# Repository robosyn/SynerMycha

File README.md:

# SynerMycha

Projekt micromouse'a

## BOM

|Qty|Value|Device|Package|Parts|Description|
|---|-----|------|-------|-----|-----------|
|3|Blue|LEDCHIP-LED0603|CHIP-LED0603|LED1,LED2,LED3||
|1|Red|LEDCHIPLED_0603|CHIPLED_0603|LED5||
|1||PINHD-1X2|1X02|POWER||
|1||PINHD-1X5|1X05|JP3||
|1||PINHD-2X3|2X03|JP1||
|1||SPDT-PTH-11.6X4.0MM|SPDT_PTH_11.6X4.0MM|S1||
|12|100nF|CAPACITOR_SMD_0603|C0603K|C5,C6,C16,C18,C19,C21,C23,C24,C27,C29,C31,C36||
|1|100nF|CPOL-EUSMCA|SMC_A|C1||
|7|10k|RESISTOR_SMD_0603|R0603|R8,R15,R16,R25,R26,R27,R28||
|1|16Mhz|CRYSTAL_SMALL";|Y1|12.0MHzCrystal||
|2|18pF|CAPACITOR_SMD_0603|C0603K|C8,C9||
|2|1k|R-EU_R0603|R0603|R13,R14||
|5|1k|RESISTOR_SMD_0603|R0603|R2,R3,R4,R5,R7||
|1|270|RESISTOR_SMD_0603|R0603|R6||
|7|2k2|RESISTOR_SMD_0603|R0603|R1,R9,R10,R11,R12,R23,R24||
|3|330|R-EU_R0402|R0402|R17,R18,R19||
|5|33uF|CPOL-EUC|PANASONIC_C|C3,C4,C7,C32,C34||
|2|ACS711|ACS712|SOIC127P600X175-8N|IC3,IC4||
|5|ADAFRUIT-VCNL4010|ADAFRUIT-VCNL4010|ADAFRUIT-VCNL4010|U$7,U$8,U$9,U$10,U$11||
|5|BC847|BC847|SOT23|T1,T2,T3,T4,T5||
|1|MICROMATCH-6|MICROMATCH-6|MICROMATCH-6|PROG-SWDIO||
|1|SPST-SMD-6.2MM|SPST-SMD-6.2MM|SPST_SMD_6.2MM|S2||
|2|AS5040|AS5040|AS5040|U$13,U$14||
|1|STM32F411RCT6|STM32F411RCT6|LQFP64|IC7||
|1|SWS004|SWS004|SMS-004|S3||
|2|TLE9201SG|TLE9201SG|PG-DSO-12-9|IC5,IC6||
|1|3V3|V_REG_317-DPACK|V-REG_DPACK|U2||
|2|N20BT06100:1|N20BT06100:1||||
|2|RW2isolarbotics|RW2isolarbotics||||
|2|300mAh|LiPol,Dualsky||||

## Linki do niektórych części

| Nazwa |kamami ID |cena (botland) |botland |electropark |tme |
| ------|:-----:|:-------------:|:------:|:----------:|:--:|
| N20 BT06              | 562730 | 19.9zł| https://botland.com.pl/pl/silniki-micro-n20-seria-mp-medium-power/12545-silnik-n20-bt05-micro-501-625rpm-12v.html | tylko oryginalne |  tylko oryginalne pololu|
| RW2i solarbotics      | 195993 | 24.9zł| https://botland.com.pl/pl/kola-z-oponami/24-kolo-solarbotics-rw2i-mocowane-wewnetrznie.html      | chwilowo niedostpne | brak|
| lipol 300mah dualsky  | brak   | 22.5zł| https://botland.com.pl/pl/akumulatory-li-pol/7876-pakiet-li-pol-dualsky-300mah-30c-2s-74v-6941047107403.html?search_query=300mAh&results=3    | wycofany | brak |
| stm32f411             | 233365 | brak  | chwilowo niedostępnu| 27.65 zł|https://www.tme.eu/pl/details/stm32f411rct6/mikrokontrolery-st/stmicroelectronics/|
| TLE9201               | brak   | brak  | brak |13.93zł| https://www.tme.eu/pl/details/tle9201sgauma1/drivery-silnikowe-i-pwm/infineon-technologies/ |
| VCNL4010              | brak   | 44zł  |   https://botland.com.pl/pl/cyfrowe-czujniki-odleglosci/4969-adafruit-vcnl4010-czujnik-odleglosci-i-swiatla-20cm-i2c.html?search_query=vcnl4010&results=1| |tylko chip bez płytki na specjalne zamówienie |

~ oferta: 
~ 35zł https://www.elfadistrelec.pl/pl/czujnik-zblizeniowy-swiatla-vcnl4010-adafruit-466/p/30139237
plus ~50 za przesyłke
TLE9210 dostępne w labie

### CADLAB 

View this project on [CADLAB.io](https://cadlab.io/project/1503).

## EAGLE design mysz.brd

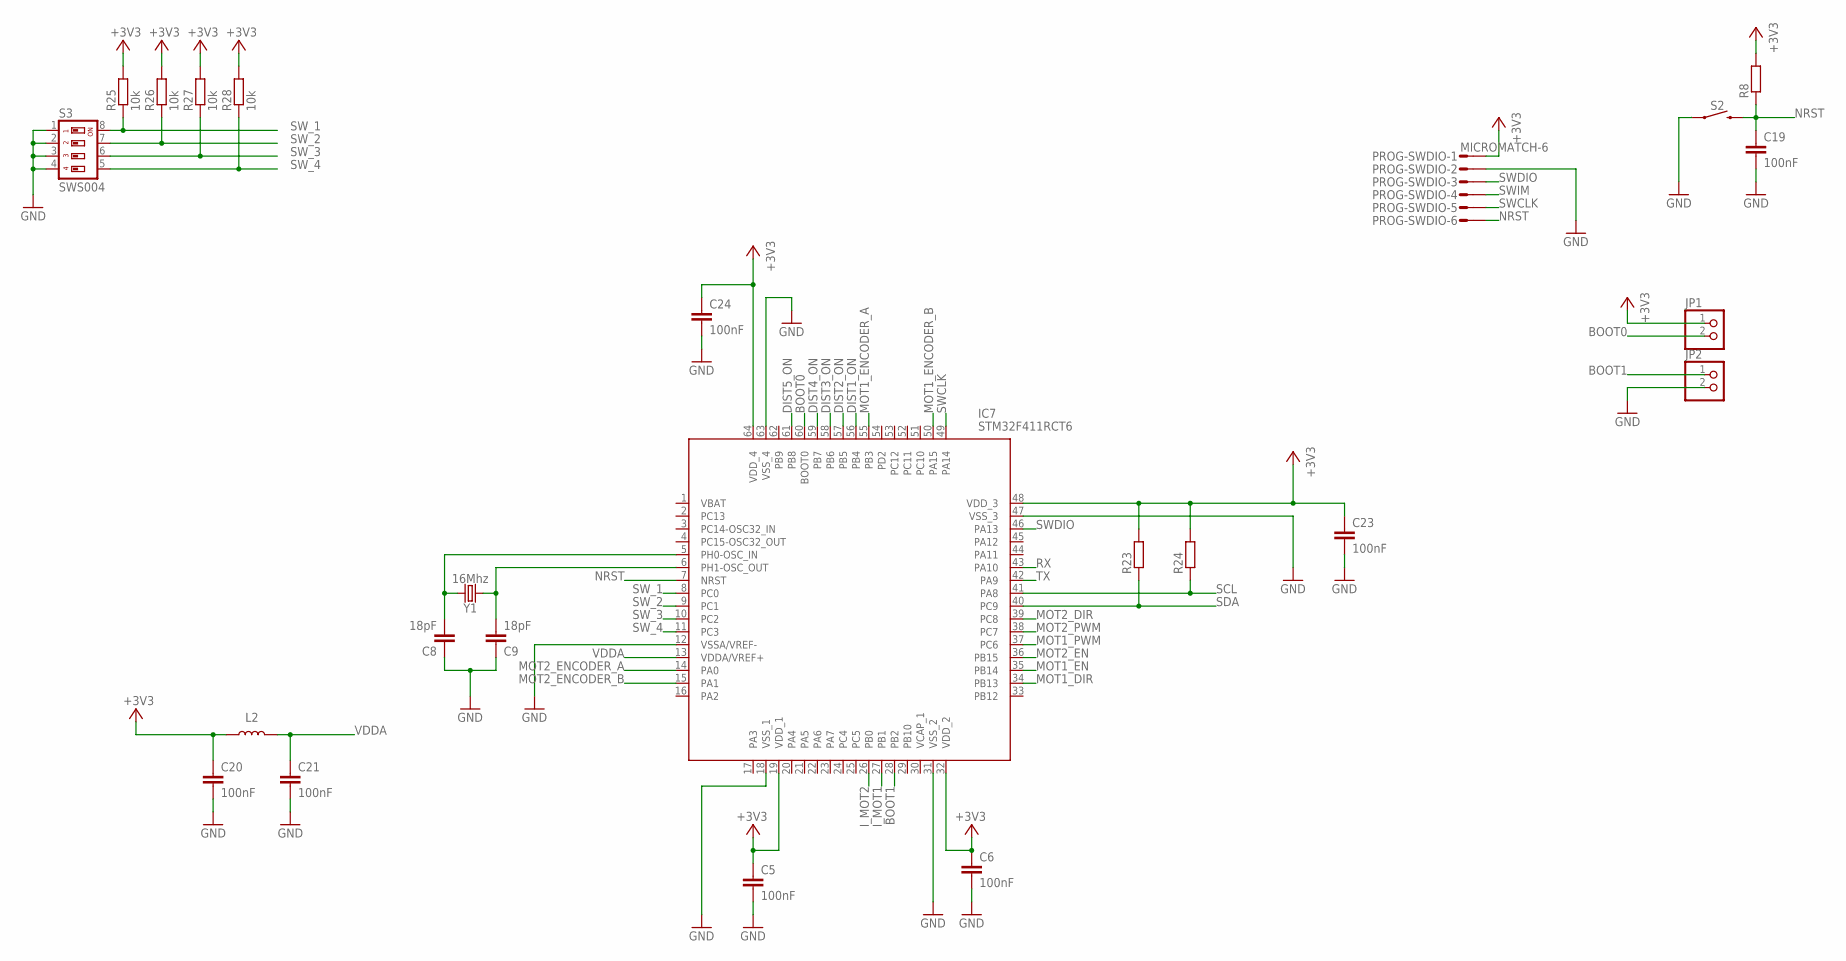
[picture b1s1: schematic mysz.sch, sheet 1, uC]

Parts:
C5, C6, C19, C20, C21, C23, C24: 100nF; C0603K
C8, C9: 18pF; C0603K
IC7: STM32F411RCT6; QFP50P1200X1200X160-64N
JP1, JP2: PINHD-1X2; 1X02
L2: INDUCTOR-0603; R0603
PROG-SWDIO: MICROMATCH-6
R8, R23, R24: RESISTOR_SMD_0603; R0603
R25, R26, R27, R28: 10k; R0603
S2: MOMENTARY-SWITCH-SPST-SMD-6.2MM_TALL; TACTILE_SWITCH_SMD_6.2MM_TALL
S3: SWS004; SMS-004
Y1: 16Mhz; CRYSTAL-SMD-5X3.2-4PAD

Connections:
+3V3: C5.1, C6.1, C20.1, C23.1, C24.1, IC7.19 (VDD_1), IC7.32 (VDD_2), IC7.48 (VDD_3), IC7.64 (VDD_4), JP1.1, L2.1, PROG-SWDIO.1, R8.2, R23.2, R24.2, R25.2, R26.2, R27.2, R28.2; also elsewhere on the board
BOOT0: IC7.60 (BOOT0), JP1.2
BOOT1: IC7.28 (PB2), JP2.1
DIST1_ON: IC7.56 (PB4); also elsewhere on the board
DIST2_ON: IC7.57 (PB5); also elsewhere on the board
DIST3_ON: IC7.58 (PB6); also elsewhere on the board
DIST4_ON: IC7.59 (PB7); also elsewhere on the board
DIST5_ON: IC7.61 (PB8); also elsewhere on the board
GND: C5.2, C6.2, C8.1, C9.1, C19.2, C20.2, C21.2, C23.2, C24.2, IC7.12 (VSSA/VREF-), IC7.18 (VSS_1), IC7.31 (VSS_2), IC7.47 (VSS_3), IC7.63 (VSS_4), JP2.2, PROG-SWDIO.2, S2.A1 (1), S2.A2 (1), S3.1, S3.2, S3.3, S3.4; also elsewhere on the board
I_MOT1: IC7.27 (PB1); also elsewhere on the board
I_MOT2: IC7.26 (PB0); also elsewhere on the board
MOT1_DIR: IC7.34 (PB13); also elsewhere on the board
MOT1_EN: IC7.35 (PB14); also elsewhere on the board
MOT1_ENCODER_A: IC7.55 (PB3); also elsewhere on the board
MOT1_ENCODER_B: IC7.50 (PA15); also elsewhere on the board
MOT1_PWM: IC7.37 (PC6); also elsewhere on the board
MOT2_DIR: IC7.39 (PC8); also elsewhere on the board
MOT2_EN: IC7.36 (PB15); also elsewhere on the board
MOT2_ENCODER_A: IC7.14 (PA0); also elsewhere on the board
MOT2_ENCODER_B: IC7.15 (PA1); also elsewhere on the board
MOT2_PWM: IC7.38 (PC7); also elsewhere on the board
NRST: C19.1, IC7.7 (NRST), PROG-SWDIO.6, R8.1, S2.B1 (2), S2.B2 (2)
RCC_OSC_IN: C8.2, IC7.5 (PH0-OSC_IN), Y1.3 (2)
RCC_OSC_OUT: C9.2, IC7.6 (PH1-OSC_OUT), Y1.1
RX: IC7.43 (PA10)
SCL: IC7.41 (PA8), R24.1; also elsewhere on the board
SDA: IC7.40 (PC9), R23.1; also elsewhere on the board
SWCLK: IC7.49 (PA14), PROG-SWDIO.5
SWDIO: IC7.46 (PA13), PROG-SWDIO.3
SWIM: PROG-SWDIO.4
SW_1: IC7.8 (PC0), R25.1, S3.8
SW_2: IC7.9 (PC1), R26.1, S3.7
SW_3: IC7.10 (PC2), R27.1, S3.6
SW_4: IC7.11 (PC3), R28.1, S3.5
TX: IC7.42 (PA9)
VDDA: C21.1, IC7.13 (VDDA/VREF+), L2.2

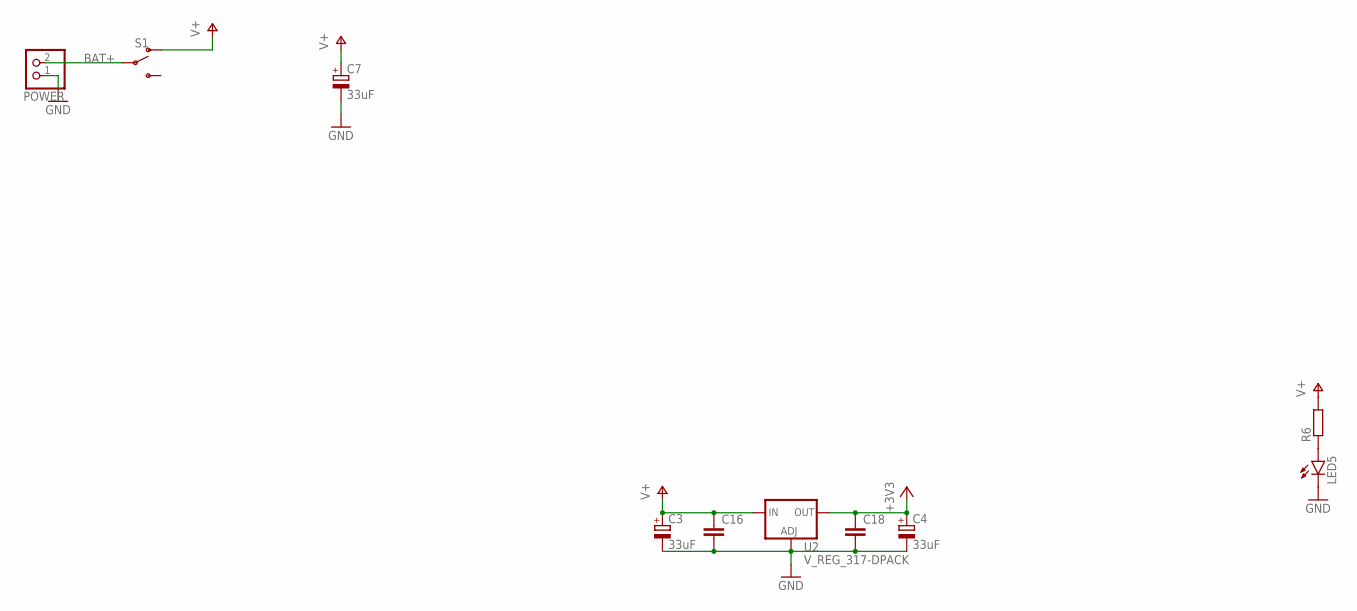
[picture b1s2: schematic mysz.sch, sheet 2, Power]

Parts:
C3, C4, C7: 33uF; PANASONIC_C
C16, C18: CAPACITOR_SMD_0603; C0603K
LED5: LEDCHIPLED_0603; CHIPLED_0603
POWER: PINHD-1X2; 1X02
R6: RESISTOR_SMD_0603; R0603
S1: SWITCH-SPDT-PTH-11.6X4.0MM; SWITCH_SPDT_PTH_11.6X4.0MM
U2: V_REG_317-DPACK; V-REG_DPACK

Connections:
+3V3: C4.+, C18.1, U2.4 (OUT); also elsewhere on the board
BAT+: POWER.2, S1.2
GND: C3.-, C4.-, C7.-, C16.2, C18.2, LED5.C, POWER.1, U2.1 (ADJ); also elsewhere on the board
unnamed: LED5.A, R6.1
V+: C3.+, C7.+, C16.1, R6.2, S1.1 (O), U2.3 (IN); also elsewhere on the board

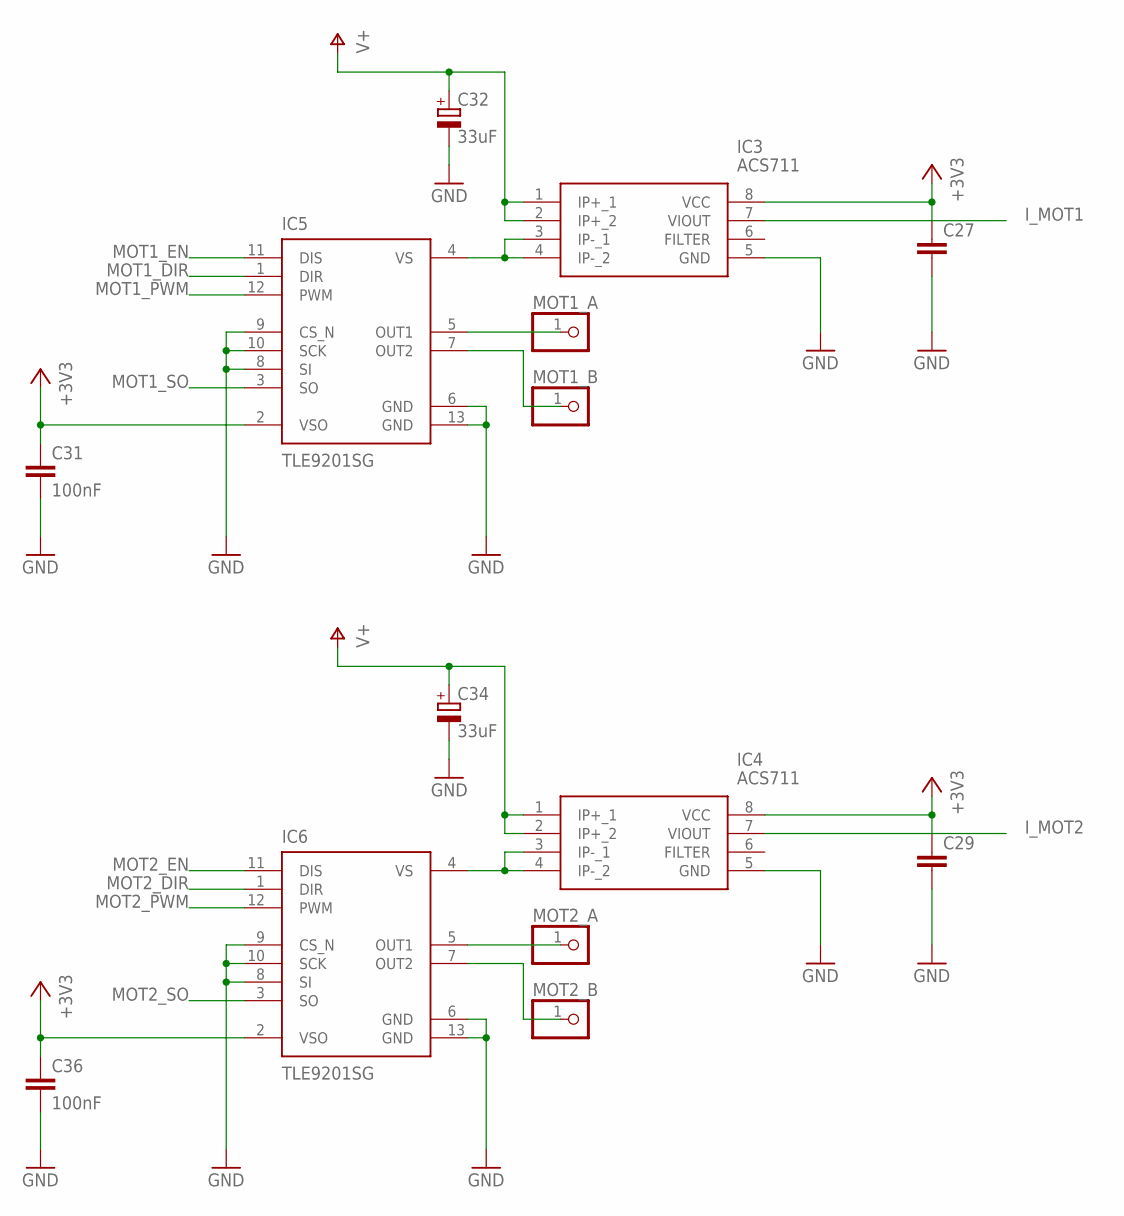
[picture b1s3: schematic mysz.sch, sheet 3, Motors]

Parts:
C27, C29: CAPACITOR_SMD_0603; C0603K
C31, C36: 100nF; C0603K
C32, C34: 33uF; PANASONIC_C
IC3, IC4: ACS711; SOIC127P600X175-8N
IC5, IC6: TLE9201SG; PG-DSO-12-9
MOT1_A, MOT1_B, MOT2_A, MOT2_B: PINHD-1X1; 1X01

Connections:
+3V3: C27.1, C29.1, C31.1, C36.1, IC3.8 (VCC), IC4.8 (VCC), IC5.2 (VSO), IC6.2 (VSO); also elsewhere on the board
GND: C27.2, C29.2, C31.2, C32.-, C34.-, C36.2, IC3.5 (GND), IC4.5 (GND), IC5.6 (GND), IC5.8 (SI), IC5.9 (CS_N), IC5.10 (SCK), IC5.13 (GND), IC6.6 (GND), IC6.8 (SI), IC6.9 (CS_N), IC6.10 (SCK), IC6.13 (GND); also elsewhere on the board
I_MOT1: IC3.7 (VIOUT); also elsewhere on the board
I_MOT2: IC4.7 (VIOUT); also elsewhere on the board
MOT1_A: IC5.5 (OUT1), MOT1_A.1
MOT1_B: IC5.7 (OUT2), MOT1_B.1
MOT1_DIR: IC5.1 (DIR); also elsewhere on the board
MOT1_EN: IC5.11 (DIS); also elsewhere on the board
MOT1_PWM: IC5.12 (PWM); also elsewhere on the board
MOT1_SO: IC5.3 (SO)
MOT1_VS: IC3.3 (IP-_1), IC3.4 (IP-_2), IC5.4 (VS)
MOT2_A: IC6.5 (OUT1), MOT2_A.1
MOT2_B: IC6.7 (OUT2), MOT2_B.1
MOT2_DIR: IC6.1 (DIR); also elsewhere on the board
MOT2_EN: IC6.11 (DIS); also elsewhere on the board
MOT2_PWM: IC6.12 (PWM); also elsewhere on the board
MOT2_SO: IC6.3 (SO)
MOT2_VS: IC4.3 (IP-_1), IC4.4 (IP-_2), IC6.4 (VS)
V+: C32.+, C34.+, IC3.1 (IP+_1), IC3.2 (IP+_2), IC4.1 (IP+_1), IC4.2 (IP+_2); also elsewhere on the board

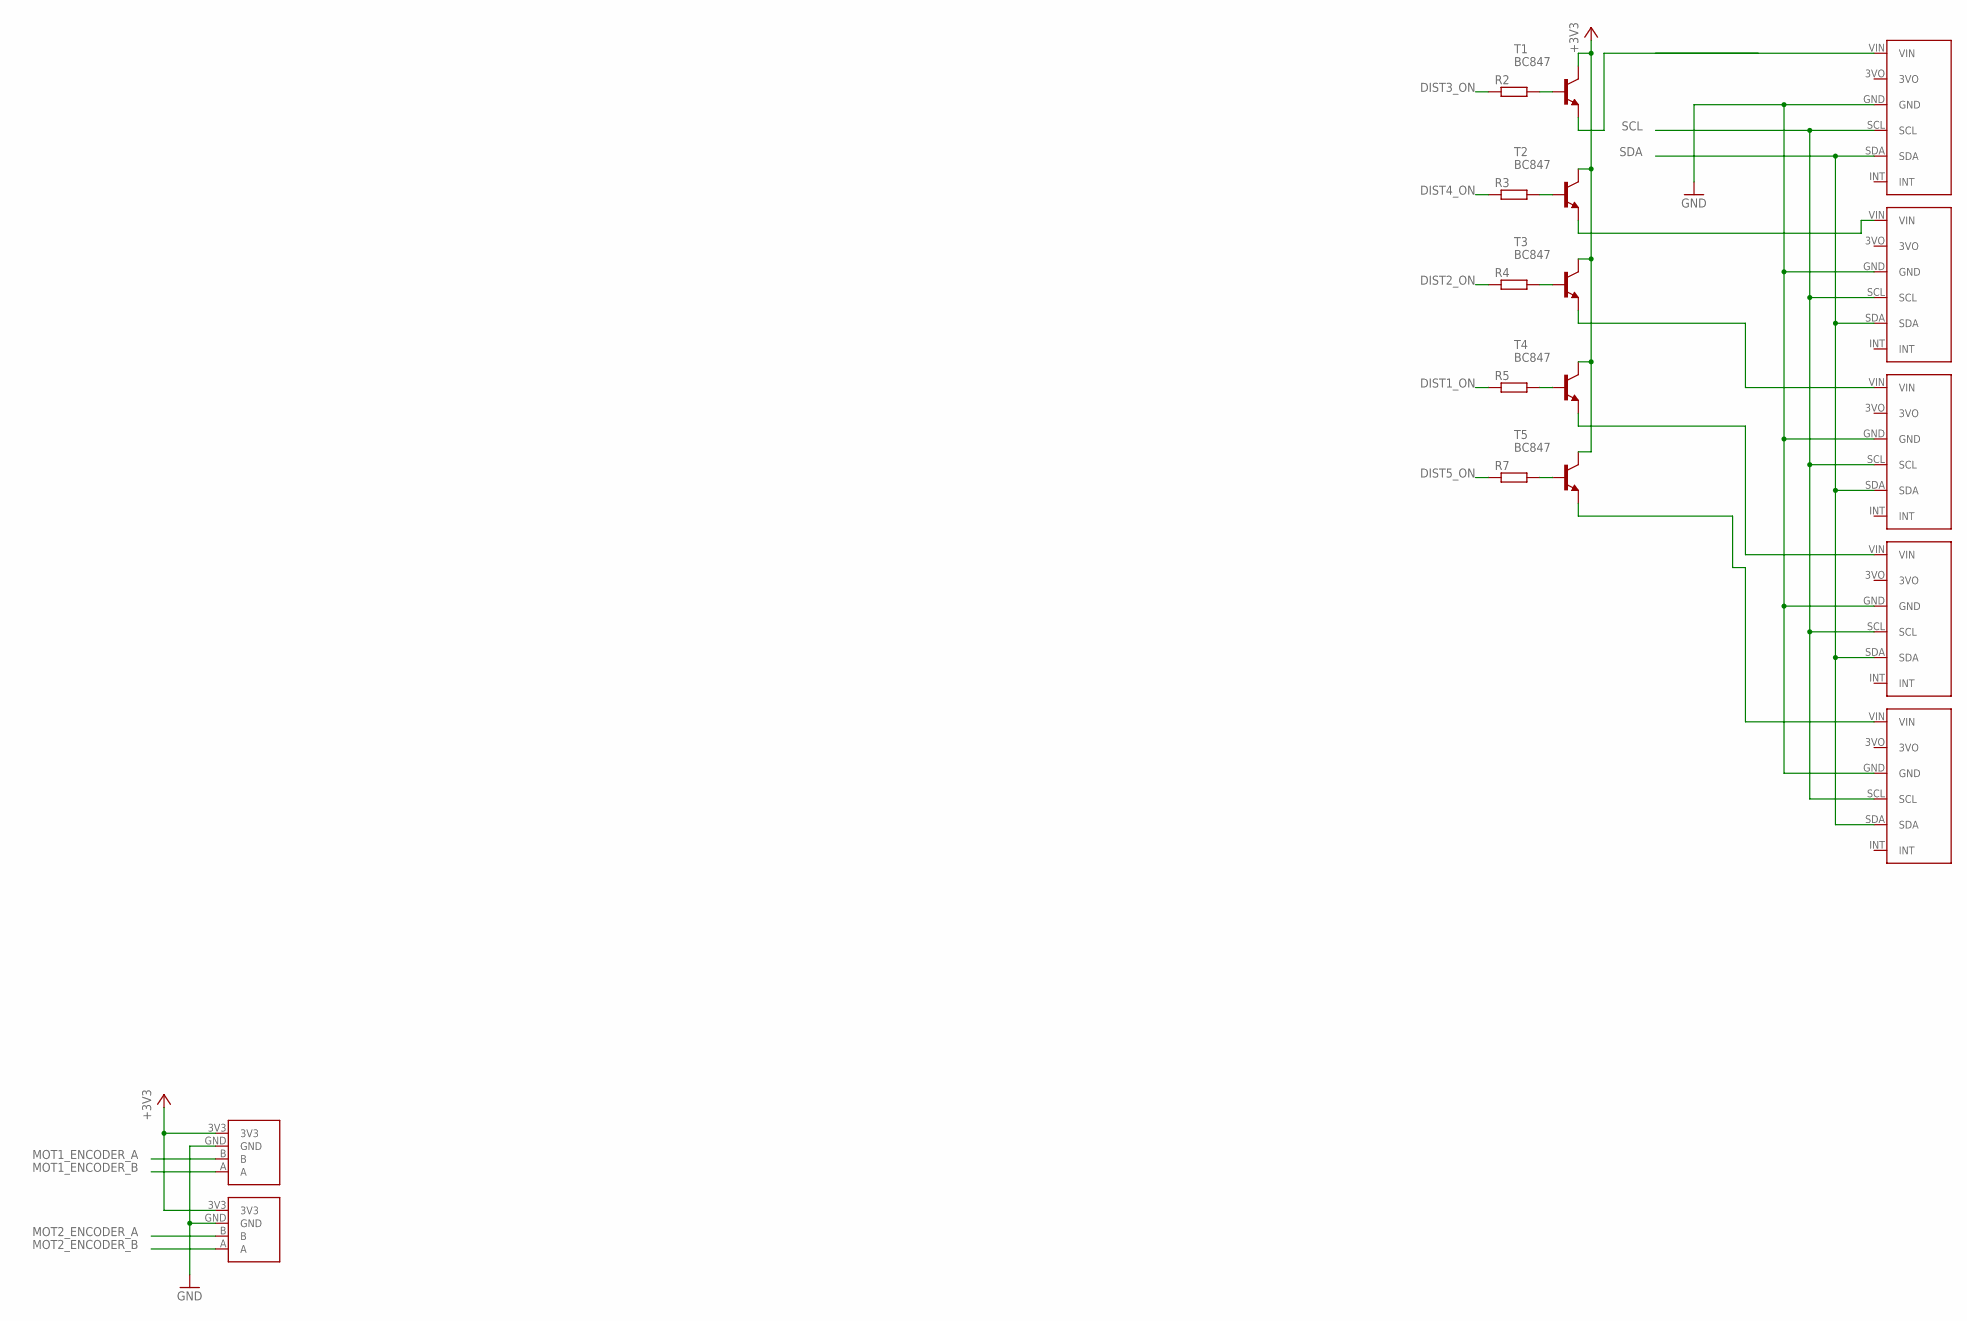
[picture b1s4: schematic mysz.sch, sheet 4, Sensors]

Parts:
R2, R3, R4, R5, R7: RESISTOR_SMD_0603; R0603
T1, T2, T3, T4, T5: BC847; SOT23
U$7, U$8, U$9, U$10, U$11: ADAFRUIT-VCNL4010
U$13, U$14: PRIV-AS5040

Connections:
+3V3: T1.3 (C), T2.3 (C), T3.3 (C), T4.3 (C), T5.3 (C), U$13.3V3, U$14.3V3; also elsewhere on the board
DIST1_ON: R5.1; also elsewhere on the board
DIST2_ON: R4.1; also elsewhere on the board
DIST3_ON: R2.1; also elsewhere on the board
DIST4_ON: R3.1; also elsewhere on the board
DIST5_ON: R7.1; also elsewhere on the board
GND: U$7.GND, U$8.GND, U$9.GND, U$10.GND, U$11.GND, U$13.GND, U$14.GND; also elsewhere on the board
MOT1_ENCODER_A: U$14.B; also elsewhere on the board
MOT1_ENCODER_B: U$14.A; also elsewhere on the board
MOT2_ENCODER_A: U$13.B; also elsewhere on the board
MOT2_ENCODER_B: U$13.A; also elsewhere on the board
unnamed: R2.2, T1.1 (B)
unnamed: R3.2, T2.1 (B)
unnamed: R4.2, T3.1 (B)
unnamed: R5.2, T4.1 (B)
unnamed: R7.2, T5.1 (B)
unnamed: T2.2 (E), U$8.VIN
unnamed: T1.2 (E), U$7.VIN
unnamed: T3.2 (E), U$9.VIN
unnamed: T4.2 (E), U$10.VIN
unnamed: T5.2 (E), U$11.VIN
SCL: U$7.SCL, U$8.SCL, U$9.SCL, U$10.SCL, U$11.SCL; also elsewhere on the board
SDA: U$7.SDA, U$8.SDA, U$9.SDA, U$10.SDA, U$11.SDA; also elsewhere on the board

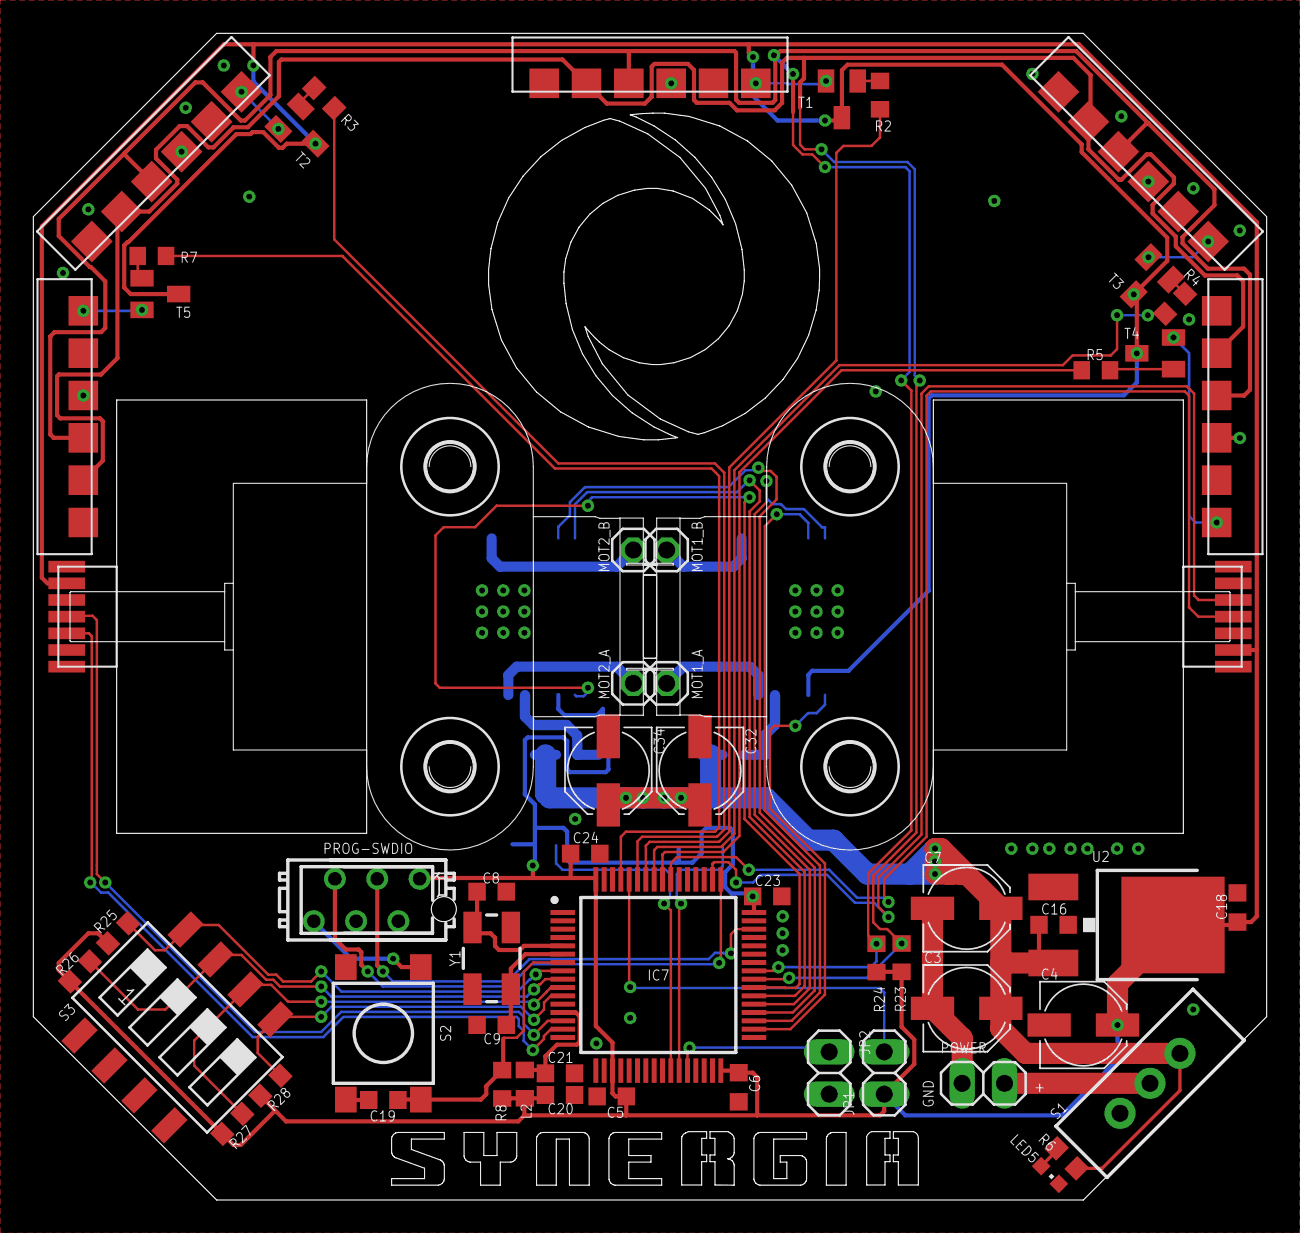
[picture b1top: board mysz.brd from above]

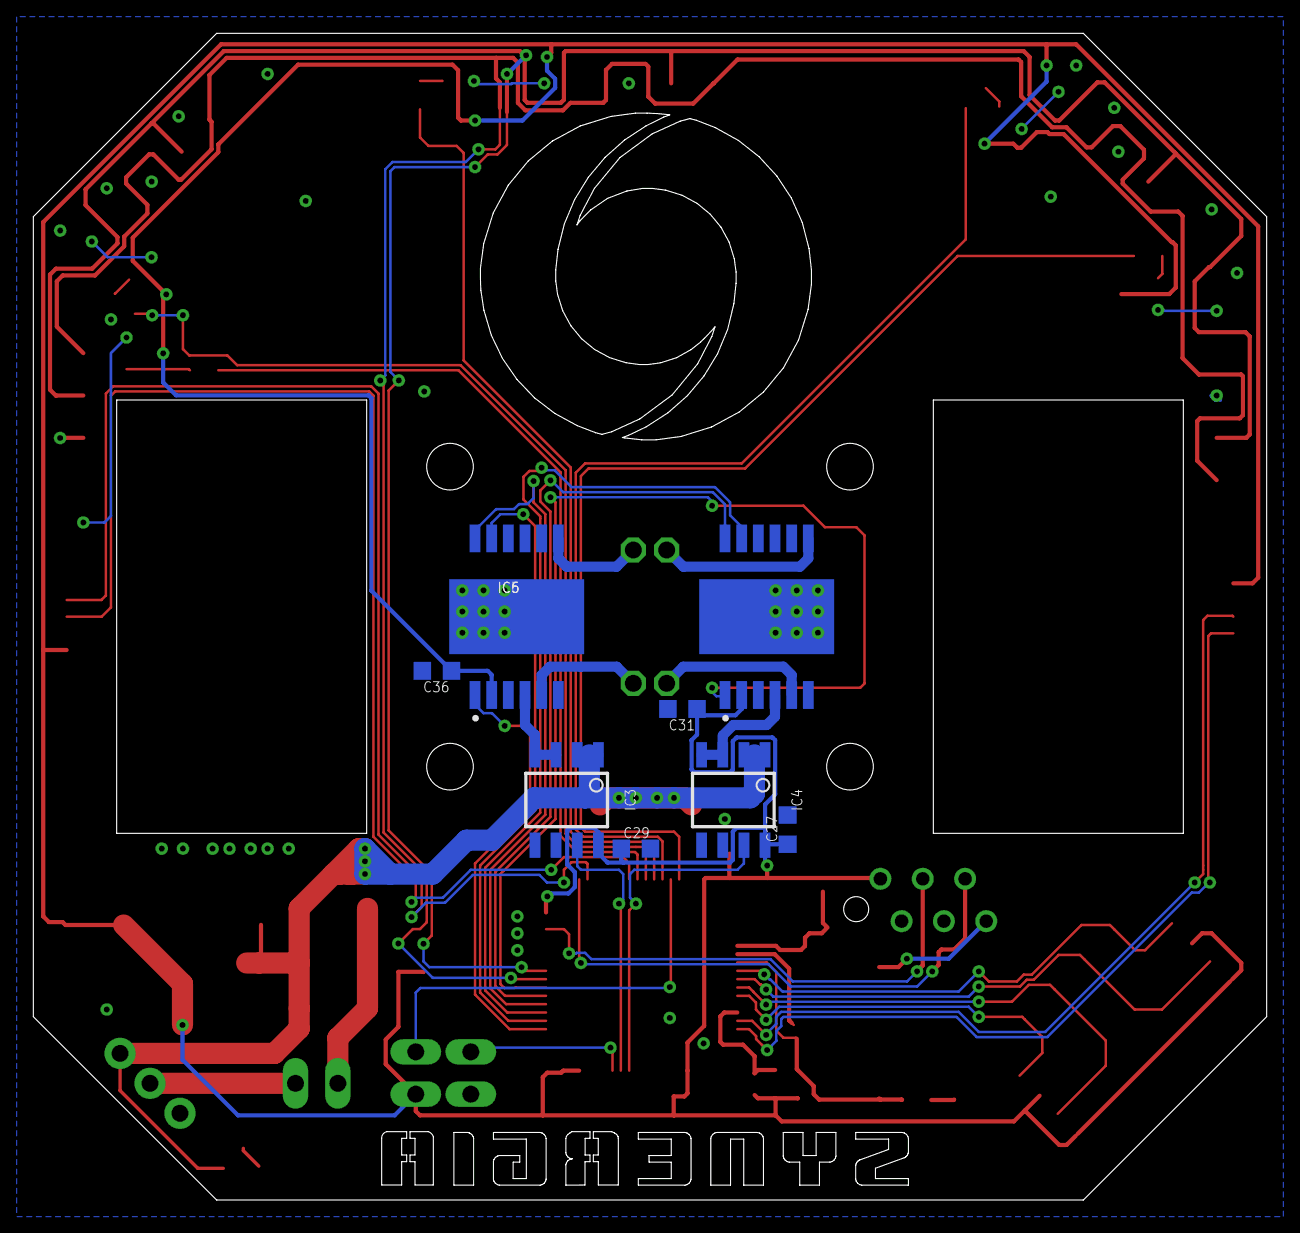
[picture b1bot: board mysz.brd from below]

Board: 2 copper layers, 74.0 x 70.0 mm, 71 parts (8 on the bottom side), 52 nets.

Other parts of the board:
U$1, U$2: POLOLU_SINGLE_SHAFT
U$3, U$4, U$5, U$6: 2,8

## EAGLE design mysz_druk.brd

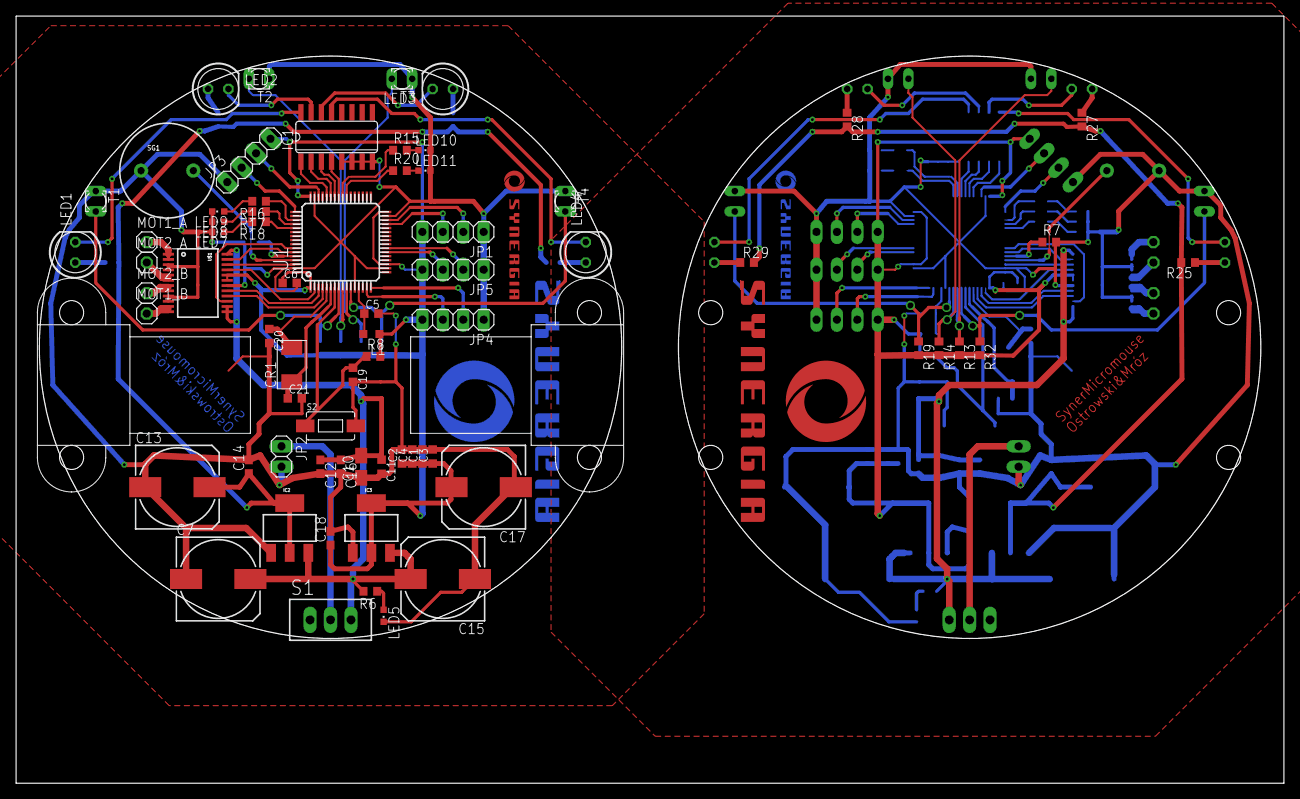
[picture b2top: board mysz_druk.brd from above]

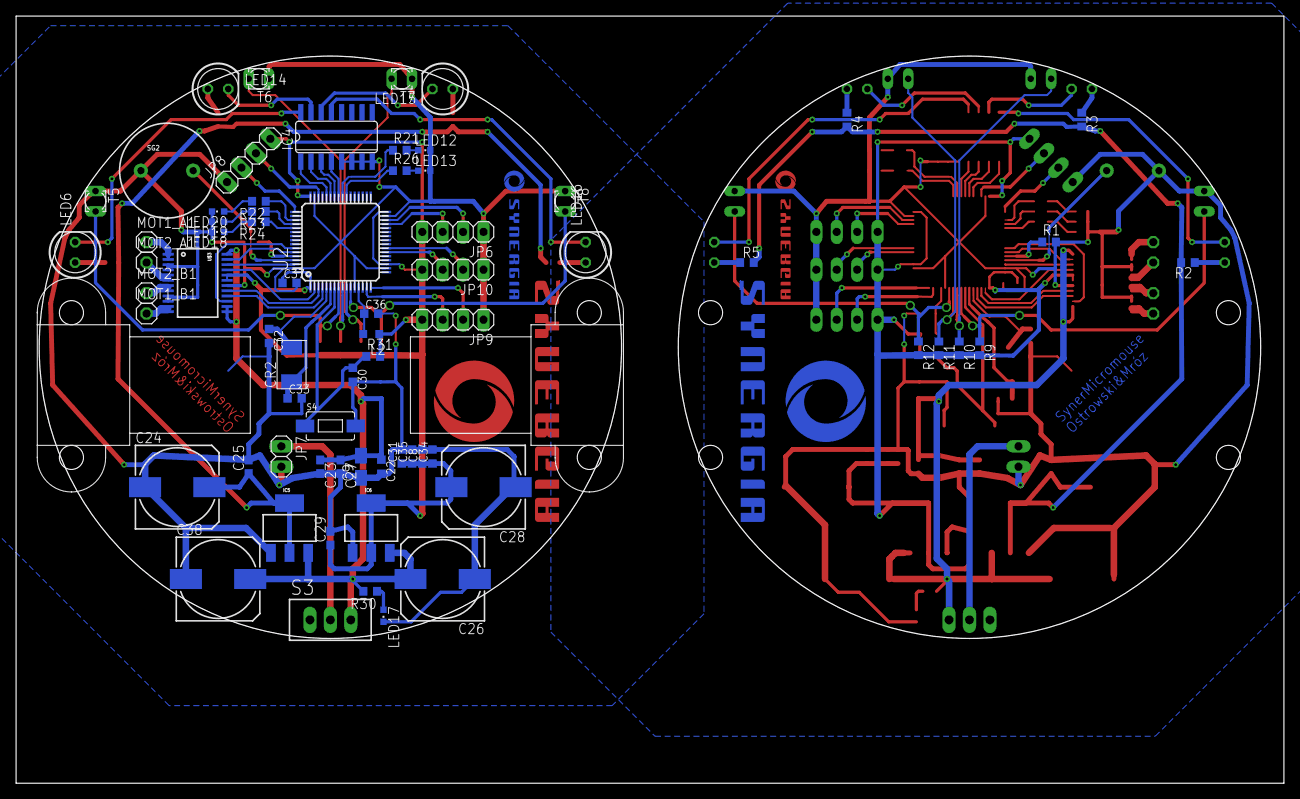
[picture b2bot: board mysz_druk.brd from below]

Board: 2 copper layers, 157.6 x 95.3 mm, 144 parts (72 on the bottom side), 112 nets.

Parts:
C1, C2, C3, C4, C5, C6, C8, C11, C19, C22, C30, C31, C34, C35, C36, C37: 100nF; C0603K
C7, C38: 100uF; 153CLV-1010
C9, C10: 10uF; A/3216-18R
C12, C14, C16, C18, C23, C25, C27, C29: 100nF; C0603
C13, C24: 33uF; 153CLV-1010
C15, C26: 47uF; 153CLV-1010
C17, C28: 10uF; 153CLV-1010
C20, C21, C32, C33: 20pF; C0603K
CR1, CR2: 8MHz; ABM7
IC1, IC4: ULN2003AD; SO16
IC2, IC3, IC5, IC6: SOT223
JP1, JP3, JP4, JP5, JP6, JP8, JP9, JP10: 1X04
JP2, JP7: 1X02
L1, L2: 10uH; L2012C
LED1, LED2, LED3, LED4, LED6, LED14, LED15, LED16: LED5MM
LED5, LED7, LED8, LED9, LED10, LED11, LED12, LED13, LED17, LED18, LED19, LED20: CHIPLED_0603
MOT1_A, MOT1_A1, MOT1_B, MOT1_B1, MOT2_A, MOT2_A1, MOT2_B, MOT2_B1: 1X01
R1, R7, R8, R31: 100k; R0603
R2, R3, R4, R5, R25, R27, R28, R29: 100R; R0603
R6, R30: 1.1k; R0603
R9, R10, R11, R12, R13, R14, R19, R32: 22k; R0603
R15, R16, R17, R18, R20, R21, R22, R23, R24, R26: 680R; R0603
S1, S3: TL32PO; TL3XPO
S2, S4: SWITCH-MOMENTARY-2-SMD-1101NE; TACTILE-SWITCH-1101NE
SG1, SG2: BUZZERPTH; BUZZER-12MM
T1, T2, T3, T4, T5, T6, T7, T8: BPX81
U1, U2: STM32F10XRXT6; TQFP64
U$1, U$3: TB6621FNG; SSOP24
U$2, U$9: SYNERGIA_LOGO_V_30MM
U$4, U$5, U$7, U$8: HP_NM
U$6, U$10: SYNERGIA_LOGO_H_16MM

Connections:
+3V1: C8.1, C28.+, C29.1, C31.1, C34.1, C35.1, C37.1, IC6.2, IC6.4, JP6.4, JP8.4, JP9.4, JP10.4, L2.1, R13.2, R14.2, R19.2, R31.2, R32.2, U2.1, U2.19, U2.32, U2.48, U2.64, U$3.19, U$3.20
+3V3: C1.1, C2.1, C3.1, C4.1, C6.1, C17.+, C18.1, IC3.2, IC3.4, JP1.4, JP3.4, JP4.4, JP5.4, L1.1, R8.2, R9.2, R10.2, R11.2, R12.2, U1.1, U1.19, U1.32, U1.48, U1.64, U$1.19, U$1.20
+5V: C13.+, C14.1, IC2.2, IC2.4, R2.2, R3.2, R4.2, R5.2
+5V1: C24.+, C25.1, IC5.2, IC5.4, R25.2, R27.2, R28.2, R29.2
BAT+: JP2.1, S1.2
BAT+1: JP7.1, S3.2
BUZZER: SG1.+, U1.61
BUZZER1: SG2.+, U2.61
CZ1: IC1.1, U1.44
CZ1_OUT: R9.1, T1.C, U1.8
CZ1_OUT1: R32.1, T5.C, U2.8
CZ2: IC1.2, U1.43
CZ2_OUT: R10.1, T2.C, U1.9
CZ2_OUT1: R13.1, T6.C, U2.9
CZ3: IC1.3, U1.42
CZ3_OUT: R11.1, T3.C, U1.10
CZ3_OUT1: R14.1, T7.C, U2.10
CZ4: IC1.4, U1.41
CZ4_OUT: R12.1, T4.C, U1.11
CZ4_OUT1: R19.1, T8.C, U2.11
CZ5: IC4.1, U2.44
CZ6: IC4.2, U2.43
CZ7: IC4.3, U2.42
CZ8: IC4.4, U2.41
ENC1_A: JP4.3, U1.15
ENC1_A1: JP9.3, U2.15
ENC1_B: JP4.2, U1.16
ENC1_B1: JP9.2, U2.16
ENC2_A: JP5.3, U1.22
ENC2_A1: JP10.3, U2.22
ENC2_B: JP5.2, U1.23
ENC2_B1: JP10.2, U2.23
GND: C1.2, C2.2, C3.2, C4.2, C5.2, C6.2, C7.-, C10.-, C11.2, C12.2, C13.-, C14.2, C15.-, C16.2, C17.-, C18.2, C19.2, C20.2, C21.2, IC1.5, IC1.6, IC1.7, IC1.8, IC2.1, IC3.1, JP1.1, JP2.2, JP3.1, JP4.1, JP5.1, LED5.C, LED7.C, LED8.C, LED9.C, LED10.C, LED11.C, R1.2, S2.P$2, SG1.-, T1.E, T2.E, T3.E, T4.E, U1.12, U1.18, U1.31, U1.47, U1.63, U$1.3, U$1.4, U$1.9, U$1.10, U$1.18
GND1: C8.2, C9.-, C22.2, C23.2, C24.-, C25.2, C26.-, C27.2, C28.-, C29.2, C30.2, C31.2, C32.2, C33.2, C34.2, C35.2, C36.2, C37.2, C38.-, IC4.5, IC4.6, IC4.7, IC4.8, IC5.1, IC6.1, JP6.1, JP7.2, JP8.1, JP9.1, JP10.1, LED12.C, LED13.C, LED17.C, LED18.C, LED19.C, LED20.C, R7.2, S4.P$2, SG2.-, T5.E, T6.E, T7.E, T8.E, U2.12, U2.18, U2.31, U2.47, U2.63, U$3.3, U$3.4, U$3.9, U$3.10, U$3.18
IN1_A: U1.2, U$1.21
IN1_A1: U2.2, U$3.21
IN1_B: U1.3, U$1.17
IN1_B1: U2.3, U$3.17
IN2_A: U1.62, U$1.22
IN2_A1: U2.62, U$3.22
IN2_B: U1.4, U$1.16
IN2_B1: U2.4, U$3.16
LED1: R20.1, U1.39
LED2: R15.1, U1.40
LED3: R16.1, U1.51
LED4: R17.1, U1.52
LED5: R18.1, U1.53
LED6: R21.1, U2.40
LED7: R22.1, U2.51
LED8: R23.1, U2.52
LED9: R24.1, U2.53
LED10: R26.1, U2.39
unnamed: R1.1, U1.60
unnamed: C5.1, L1.2, U1.13
unnamed: LED7.A, R18.2
unnamed: LED8.A, R17.2
unnamed: LED9.A, R16.2
unnamed: LED10.A, R15.2
unnamed: LED5.A, R6.1
unnamed: IC1.16, LED1.K
unnamed: MOT1_A.1, U$1.1, U$1.2
unnamed: MOT2_A.1, U$1.5, U$1.6
unnamed: MOT2_B.1, U$1.7, U$1.8
unnamed: MOT1_B.1, U$1.11, U$1.12
unnamed: IC1.15, LED2.K
unnamed: IC1.14, LED3.K
unnamed: IC1.13, LED4.K
unnamed: R7.1, U2.60
unnamed: LED1.A, R2.1
unnamed: LED2.A, R3.1
unnamed: LED3.A, R4.1
unnamed: LED4.A, R5.1
unnamed: C36.1, L2.2, U2.13
unnamed: MOT1_A1.1, U$3.1, U$3.2
unnamed: C20.1, CR1.P$2, U1.5
unnamed: C21.1, CR1.P$1, U1.6
unnamed: MOT2_A1.1, U$3.5, U$3.6
unnamed: LED11.A, R20.2
unnamed: MOT2_B1.1, U$3.7, U$3.8
unnamed: MOT1_B1.1, U$3.11, U$3.12
unnamed: IC4.16, LED6.K
unnamed: IC4.15, LED14.K
unnamed: IC4.14, LED15.K
unnamed: IC4.13, LED16.K
unnamed: LED6.A, R25.1
unnamed: LED14.A, R27.1
unnamed: LED15.A, R28.1
unnamed: LED16.A, R29.1
unnamed: C32.1, CR2.P$2, U2.5
unnamed: C33.1, CR2.P$1, U2.6
unnamed: LED18.A, R24.2
unnamed: LED19.A, R23.2
unnamed: LED20.A, R22.2
unnamed: LED12.A, R21.2
unnamed: LED13.A, R26.2
unnamed: LED17.A, R30.1
PWM_A: U1.59, U$1.23
PWM_A1: U2.59, U$3.23
PWM_B: U1.58, U$1.15
PWM_B1: U2.58, U$3.15
RESET: C19.1, R8.1, S2.P$1, U1.7
RESET1: C30.1, R31.1, S4.P$1, U2.7
RX: JP1.2, U1.30
RX1: JP6.2, U2.30
SWCLK: JP3.2, U1.49
SWCLK1: JP8.2, U2.49
SWDIO: JP3.3, U1.46
SWDIO1: JP8.3, U2.46
TX: JP1.3, U1.29
TX1: JP6.3, U2.29
V+: C7.+, C10.+, C11.1, C12.1, C15.+, C16.1, IC2.3, IC3.3, R6.2, S1.3, U$1.13, U$1.14, U$1.24
V+1: C9.+, C22.1, C23.1, C26.+, C27.1, C38.+, IC5.3, IC6.3, R30.2, S3.3, U$3.13, U$3.14, U$3.24

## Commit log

2018-11-01 Old design copy
2018-11-26 Added all planned sensors to schematic
2018-11-28 Getting smaller
2018-12-10 Finished wiring
2018-12-10 Backlink to CADLAB.io has been added.
2019-08-22 Clearing
    Deleted project from eagle, moved to kicad, fresh start
    Added Hardware/Software folders
2019-08-22 Microcontroller and others
2019-08-22 Save
2019-08-22 CubeMX init commit
2019-12-18 zaktualizowano readme o liste części
2019-12-29 zaktualizowano cene w elfadistrelec

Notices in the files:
parts and their libraries:
SparkFun-Switches: Licensing: Creative Commons ShareAlike 4.0 International - https://creativecommons.org/licenses/by-sa/4.0
SparkFun: Licensing: CC v3.0 Share-Alike You are welcome to use this library for commercial purposes.
